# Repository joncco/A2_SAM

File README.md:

# A2_SAM
Clone of the Software Automatic Mouth card for Apple II.  Despite being supposedly "software only speech synthesizer", the Apple II version required a card containing a DAC.  A hack exists that does not need the card and uses the internal speaker, but this one has a lot of distortion.

SAM_libraries contain schematic symbols and footprints that are not in the standard kicad libraries.

SAM.zip contains the gerbers for the latest release.

Updates:

06/01/2025
Fixed slot dimensions (original was too big)

Removed solder mask from area around slot pins.

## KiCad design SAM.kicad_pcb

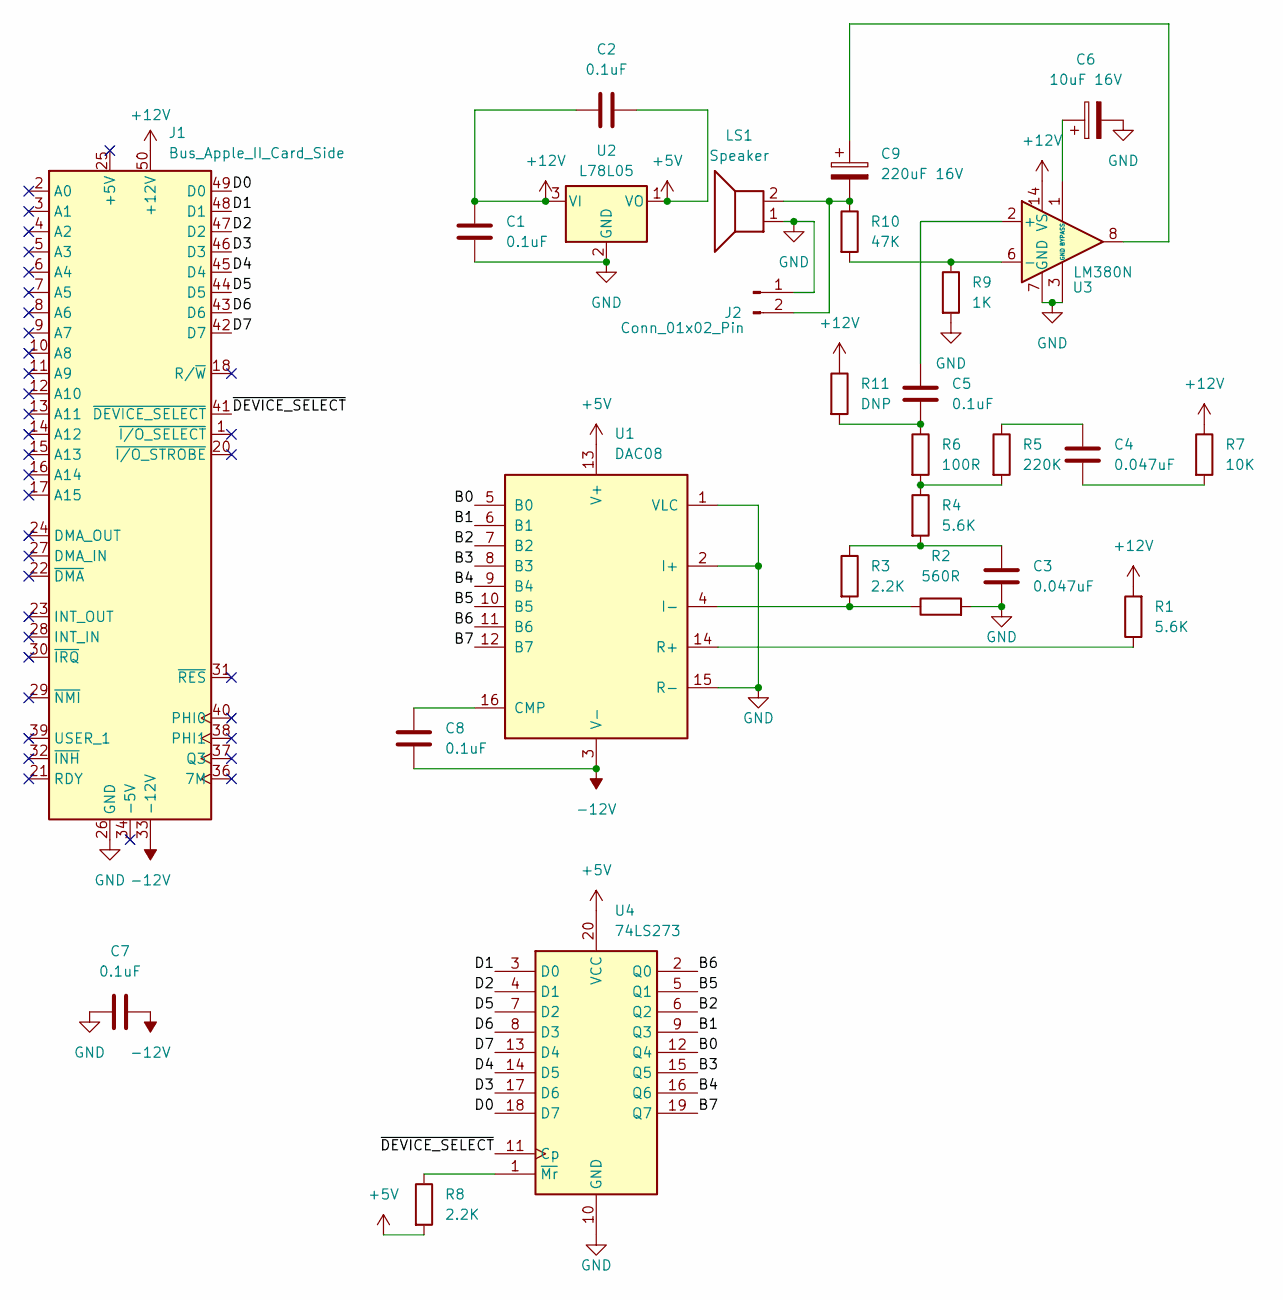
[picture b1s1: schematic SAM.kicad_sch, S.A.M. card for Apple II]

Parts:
C1, C2, C5, C7, C8: 0.1uF; Ceramic_CAP1
C3, C4: 0.047uF; Ceramic_CAP2
C6: 10uF 16V; CP_Radial_Tantal_D4.5mm_P3.7
C9: 220uF 16V; CP_Radial_Tantal_D4.5mm_P4.3
J1: Bus_Apple_II_Card_Side; BUS_A2
J2: Conn_01x02_Pin; PinHeader_1x02_P1.27mm_Horizontal
LS1: Speaker
R1, R4: 5.6K; R_Axial_DIN0207_L6.3mm_D2.5mm_P9.5mm_Horizontal
R2: 560R; R_Axial_DIN0207_L6.3mm_D2.5mm_P9.5mm_Horizontal
R3, R8: 2.2K; R_Axial_DIN0207_L6.3mm_D2.5mm_P9.5mm_Horizontal
R5: 220K; R_Axial_DIN0207_L6.3mm_D2.5mm_P9.5mm_Horizontal
R6: 100R; R_Axial_DIN0207_L6.3mm_D2.5mm_P8.0mm_Horizontal
R7: 10K; R_Axial_DIN0207_L6.3mm_D2.5mm_P9.5mm_Horizontal
R9: 1K; R_Axial_DIN0207_L6.3mm_D2.5mm_P9.5mm_Horizontal
R10: 47K; R_Axial_DIN0207_L6.3mm_D2.5mm_P9.5mm_Horizontal
R11: DNP; R_Axial_DIN0207_L6.3mm_D2.5mm_P8.0mm_Horizontal
U1: DAC08; DIP-16_W7.62mm_LongPads
U2: L78L05; TO-92_Inline
U3: LM380N; DIP-14_W7.62mm_LongPads
U4: 74LS273; DIP-20_W7.62mm_LongPads

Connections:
+5V: C2.2, R8.2, U1.13 (V+), U2.1 (VO), U4.20 (VCC)
+12V: C1.1, C2.1, J1.50 (+12V), R1.2, R7.1, R11.1, U2.3 (VI), U3.14 (VS)
-12V: C7.2, C8.2, J1.33 (-12V), U1.3 (V-)
/B0: U1.5 (B0), U4.12 (Q4)
/B1: U1.6 (B1), U4.9 (Q3)
/B2: U1.7 (B2), U4.6 (Q2)
/B3: U1.8 (B3), U4.15 (Q5)
/B4: U1.9 (B4), U4.16 (Q6)
/B5: U1.10 (B5), U4.5 (Q1)
/B6: U1.11 (B6), U4.2 (Q0)
/B7: U1.12 (B7), U4.19 (Q7)
/D0: J1.49 (D0), U4.18 (D7)
/D1: J1.48 (D1), U4.3 (D0)
/D2: J1.47 (D2), U4.4 (D1)
/D3: J1.46 (D3), U4.17 (D6)
/D4: J1.45 (D4), U4.14 (D5)
/D5: J1.44 (D5), U4.7 (D2)
/D6: J1.43 (D6), U4.8 (D3)
/D7: J1.42 (D7), U4.13 (D4)
/~DEVICE_SELECT: J1.41 (~DEVICE_SELECT), U4.11 (Cp)
GND: C1.2, C3.2, C6.2, C7.1, J1.26 (GND), J2.1, LS1.1, R2.2, R9.2, U1.1 (VLC), U1.2 (I+), U1.15 (R-), U2.2 (GND), U3.3 (GND), U3.4 (GND), U3.5 (GND), U3.7 (GND), U3.10 (GND), U3.11 (GND), U3.12 (GND), U4.10 (GND)
unnamed: C3.1, R3.1, R4.2
unnamed: C4.1, R5.1
unnamed: C4.2, R7.2
unnamed: C5.2, R6.1, R11.2
unnamed: C9.1, U3.8
unnamed: C9.2, J2.2, LS1.2, R10.1
unnamed: R4.1, R5.2, R6.2
unnamed: C8.1, U1.16 (CMP)
unnamed: R2.1, R3.2, U1.4 (I-)
unnamed: R1.1, U1.14 (R+)
unnamed: C5.1, U3.2 (+)
unnamed: R9.1, R10.2, U3.6 (-)
unnamed: C6.1, U3.1 (BYPASS)
unnamed: R8.1, U4.1 (~Mr)

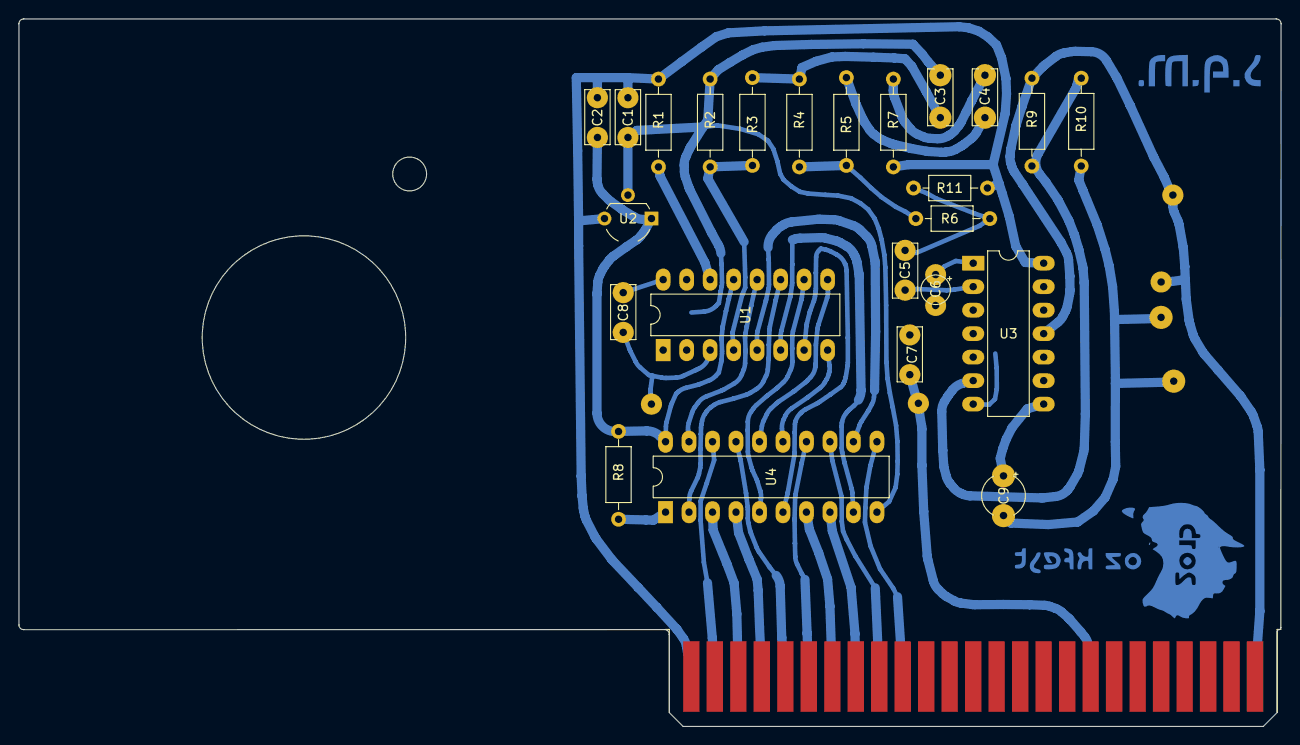
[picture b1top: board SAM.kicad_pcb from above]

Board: 2 copper layers, 136.5 x 76.5 mm, 25 parts (0 on the bottom side), 35 nets.

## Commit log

2023-11-01 Add files for human readable schematic and PCB image
2023-11-01 chamfer traces so they look like manually done
2023-11-02 Update speaker hole diameter
2023-11-06 Update remove solder mask from ozkfest and sam logo
2025-01-06 Fix Apple II slot dimensions
2025-01-06 Replot gerber file
2025-01-06 Rerender board with latest changes
2025-02-13 change 7805 to 78L05
